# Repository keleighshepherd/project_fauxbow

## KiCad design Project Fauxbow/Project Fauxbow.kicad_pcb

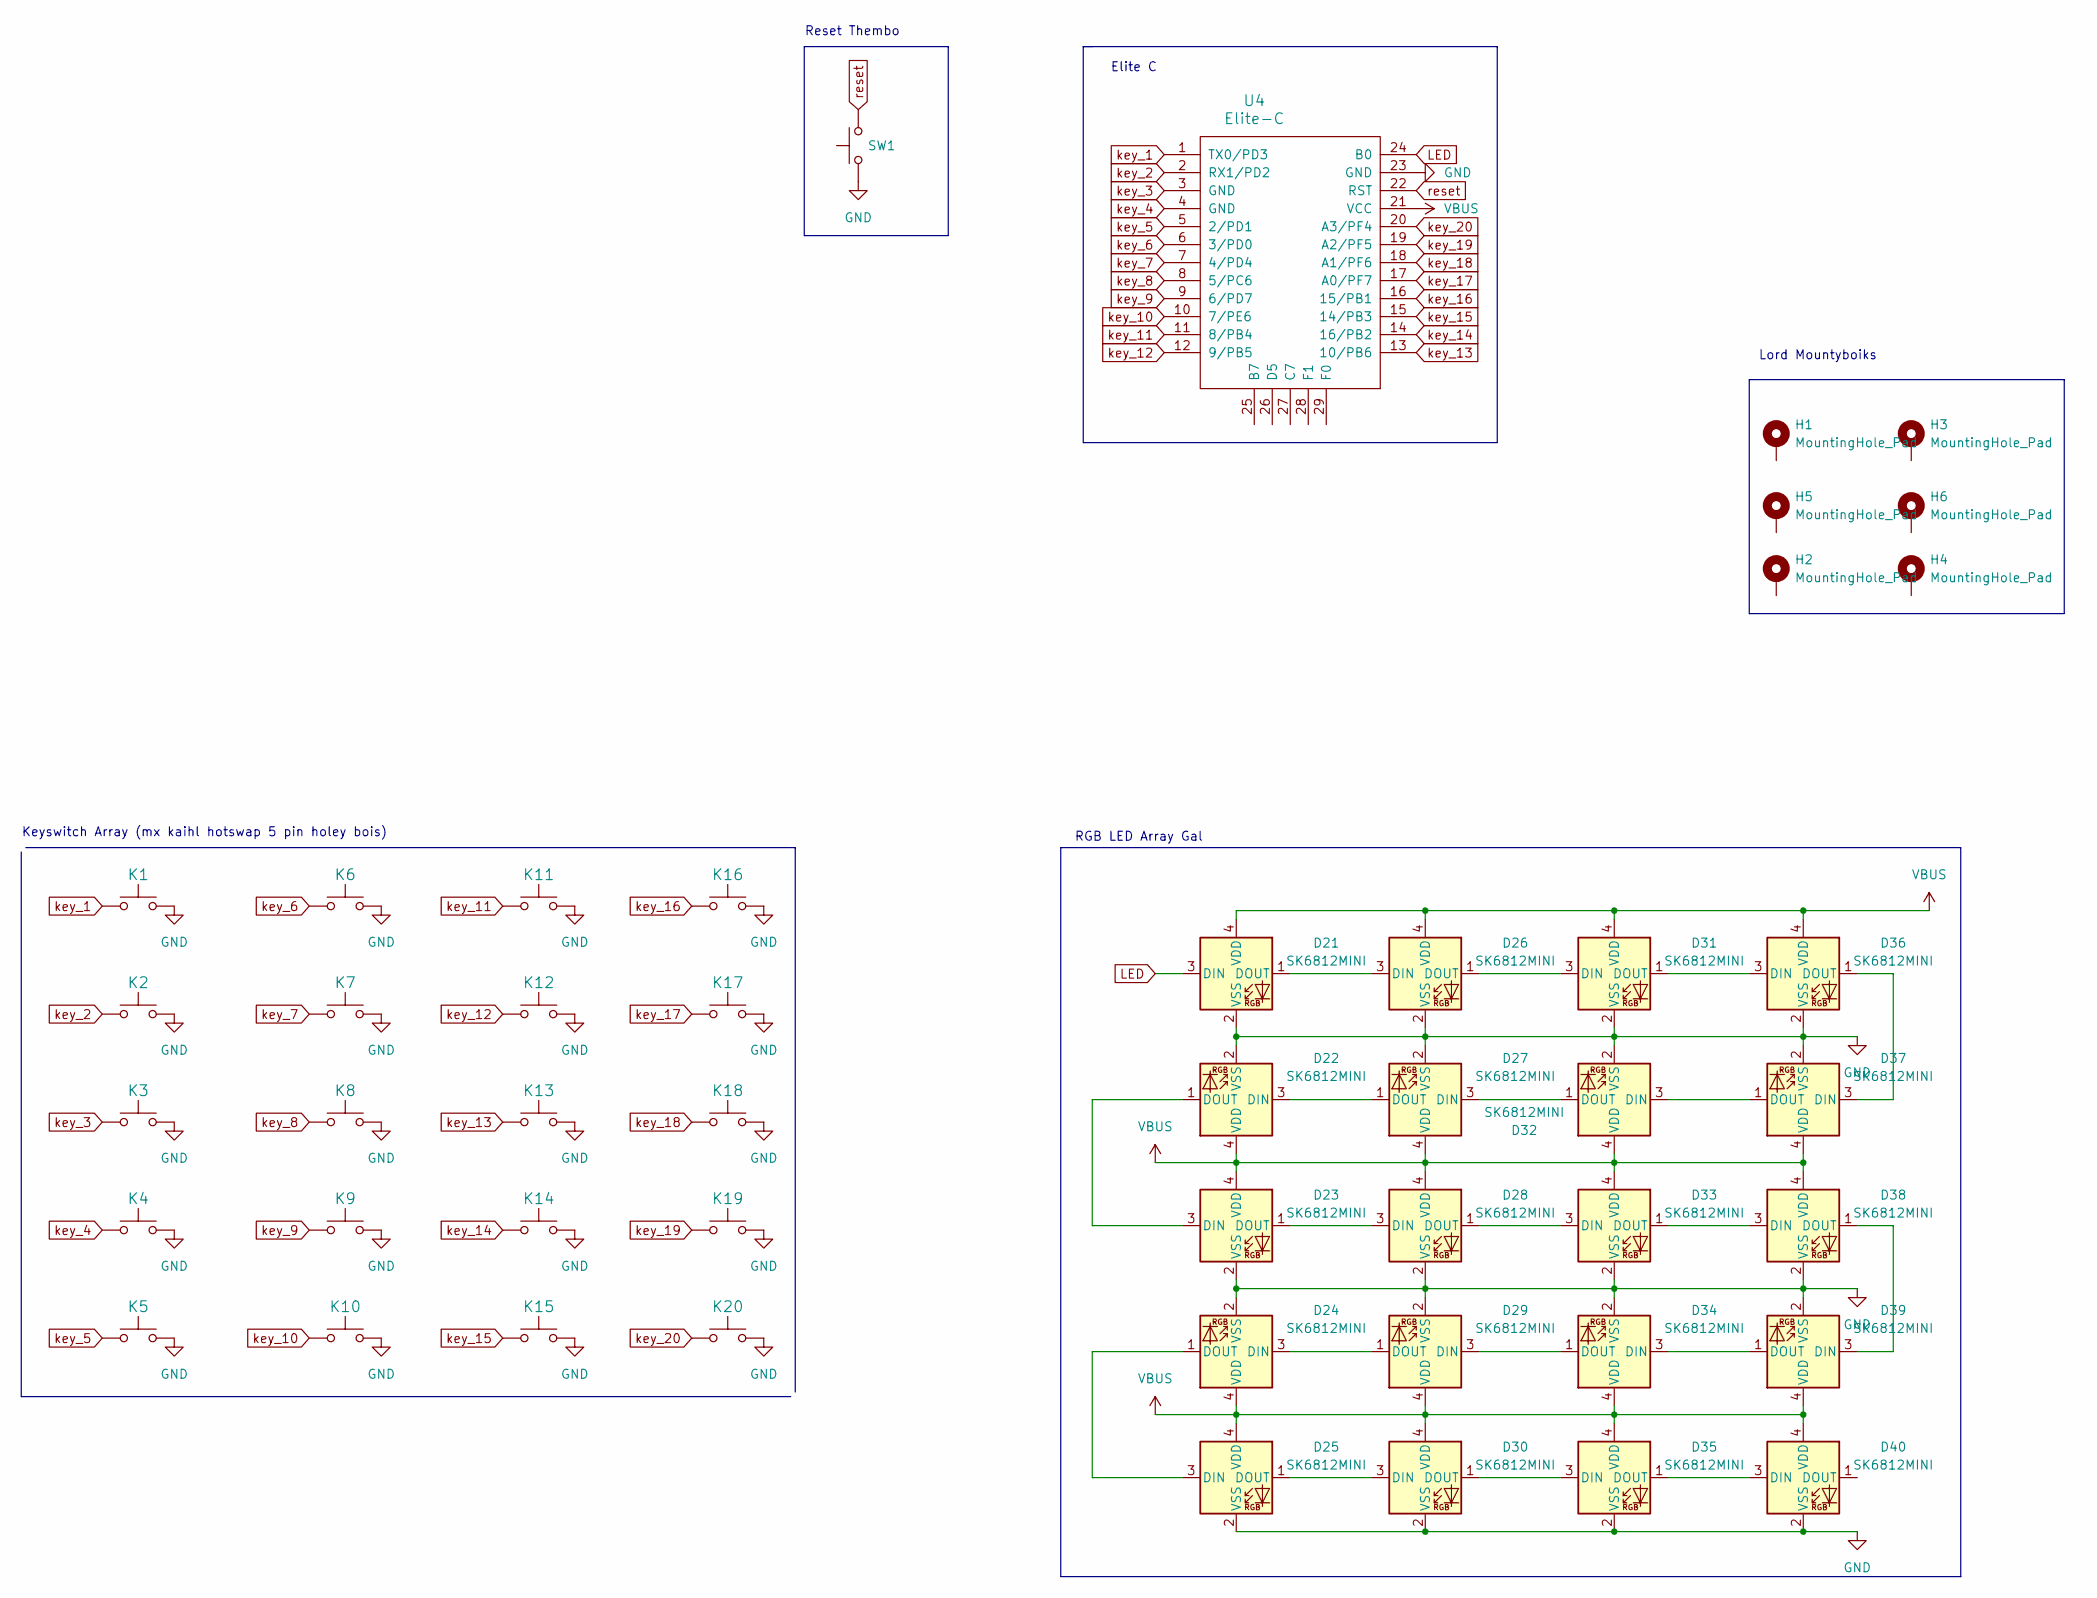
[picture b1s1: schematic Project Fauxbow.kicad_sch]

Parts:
D21, D22, D23, D24, D25, D26, D27, D28, D29, D30, D31, D32, D33, D34, D35, D36, D37, D38, D39, D40: SK6812MINI; LED_MX_6028R-FLIPPED
H1, H2, H3, H4, H5, H6: MountingHole_Pad; MountingHole_2.7mm_M2.5_ISO7380_Pad
K1, K2, K3, K4, K5, K6, K7, K8, K9, K10, K11, K12, K13, K14, K15, K16, K17, K18, K19, K20: Kailh Hotswap Socket; SW_MX_HS_1u; MPN CPG151101S11
SW1: SW_Push; SW_Tactile_SPST_Angled_MJTP1117
U4: Elite-C; Elite-C-castellated-29pin-holes

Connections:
GND: D21.2 (VSS), D22.2 (VSS), D23.2 (VSS), D24.2 (VSS), D25.2 (VSS), D26.2 (VSS), D27.2 (VSS), D28.2 (VSS), D29.2 (VSS), D30.2 (VSS), D31.2 (VSS), D32.2 (VSS), D33.2 (VSS), D34.2 (VSS), D35.2 (VSS), D36.2 (VSS), D37.2 (VSS), D38.2 (VSS), D39.2 (VSS), D40.2 (VSS), K1.1, K2.1, K3.1, K4.1, K5.1, K6.1, K7.1, K8.1, K9.1, K10.1, K11.1, K12.1, K13.1, K14.1, K15.1, K16.1, K17.1, K18.1, K19.1, K20.1, SW1.1, U4.23 (GND)
LED: D21.3 (DIN), U4.24 (B0)
unnamed: D21.1 (DOUT), D26.3 (DIN)
unnamed: D22.1 (DOUT), D23.3 (DIN)
unnamed: D22.3 (DIN), D27.1 (DOUT)
unnamed: D23.1 (DOUT), D28.3 (DIN)
unnamed: D24.1 (DOUT), D25.3 (DIN)
unnamed: D24.3 (DIN), D29.1 (DOUT)
unnamed: D25.1 (DOUT), D30.3 (DIN)
unnamed: D26.1 (DOUT), D31.3 (DIN)
unnamed: D27.3 (DIN), D32.1 (DOUT)
unnamed: D28.1 (DOUT), D33.3 (DIN)
unnamed: D29.3 (DIN), D34.1 (DOUT)
unnamed: D30.1 (DOUT), D35.3 (DIN)
unnamed: D31.1 (DOUT), D36.3 (DIN)
unnamed: D32.3 (DIN), D37.1 (DOUT)
unnamed: D33.1 (DOUT), D38.3 (DIN)
unnamed: D34.3 (DIN), D39.1 (DOUT)
unnamed: D35.1 (DOUT), D40.3 (DIN)
unnamed: D36.1 (DOUT), D37.3 (DIN)
unnamed: D38.1 (DOUT), D39.3 (DIN)
VBUS: D21.4 (VDD), D22.4 (VDD), D23.4 (VDD), D24.4 (VDD), D25.4 (VDD), D26.4 (VDD), D27.4 (VDD), D28.4 (VDD), D29.4 (VDD), D30.4 (VDD), D31.4 (VDD), D32.4 (VDD), D33.4 (VDD), D34.4 (VDD), D35.4 (VDD), D36.4 (VDD), D37.4 (VDD), D38.4 (VDD), D39.4 (VDD), D40.4 (VDD), U4.21 (VCC)
key_1: K1.2, U4.1 (TX0/PD3)
key_2: K2.2, U4.2 (RX1/PD2)
key_3: K3.2, U4.3 (GND)
key_4: K4.2, U4.4 (GND)
key_5: K5.2, U4.5 (2/PD1)
key_6: K6.2, U4.6 (3/PD0)
key_7: K7.2, U4.7 (4/PD4)
key_8: K8.2, U4.8 (5/PC6)
key_9: K9.2, U4.9 (6/PD7)
key_10: K10.2, U4.10 (7/PE6)
key_11: K11.2, U4.11 (8/PB4)
key_12: K12.2, U4.12 (9/PB5)
key_13: K13.2, U4.13 (10/PB6)
key_14: K14.2, U4.14 (16/PB2)
key_15: K15.2, U4.15 (14/PB3)
key_16: K16.2, U4.16 (15/PB1)
key_17: K17.2, U4.17 (A0/PF7)
key_18: K18.2, U4.18 (A1/PF6)
key_19: K19.2, U4.19 (A2/PF5)
key_20: K20.2, U4.20 (A3/PF4)
reset: SW1.2, U4.22 (RST)

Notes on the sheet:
Reset Thembo
Lord Mountyboiks
Keyswitch Array (mx kaihl hotswap 5 pin holey bois)
RGB LED Array Gal
Elite C

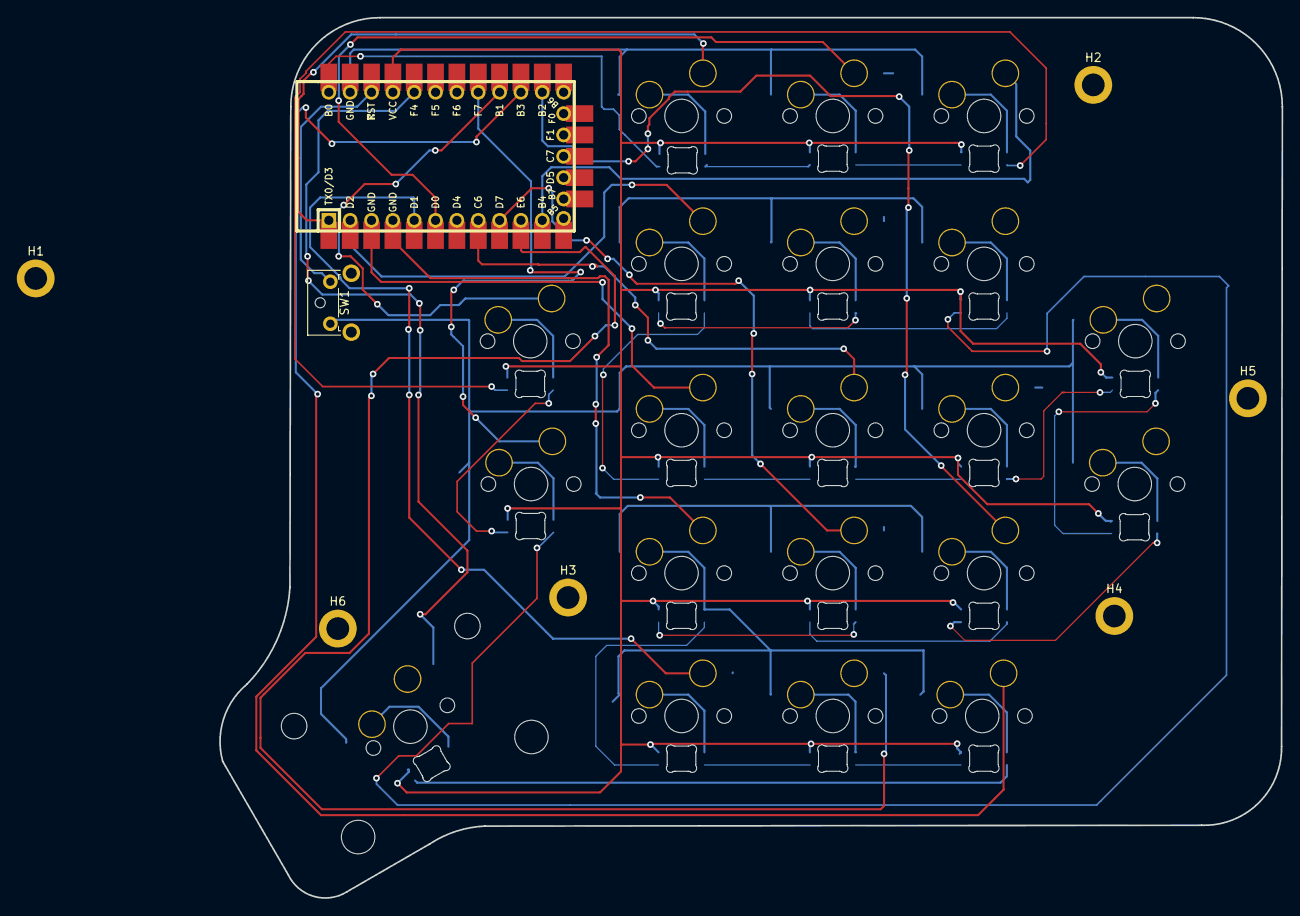
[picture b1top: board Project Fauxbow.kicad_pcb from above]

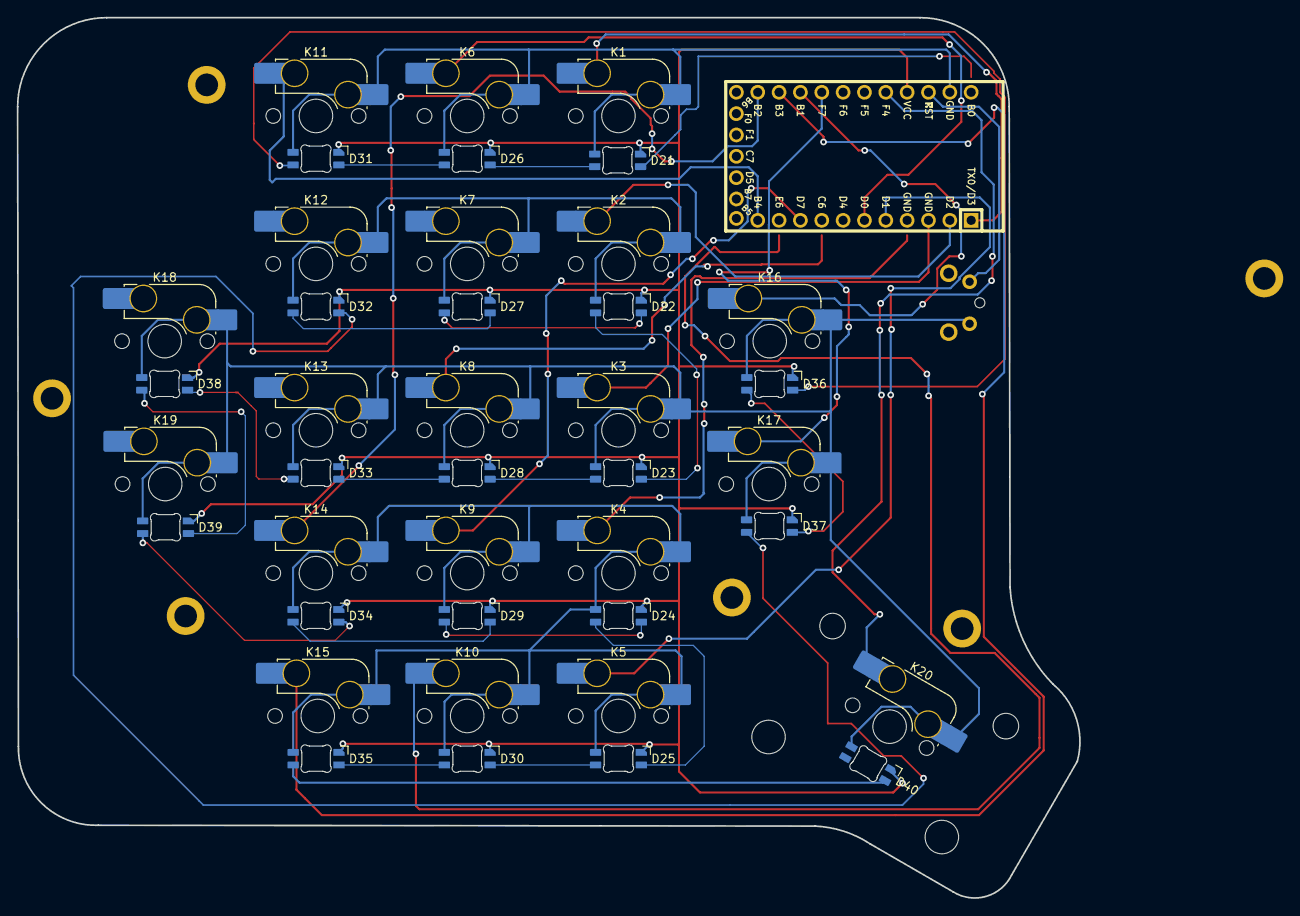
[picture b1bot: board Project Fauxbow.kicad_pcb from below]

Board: 2 copper layers, 126.4 x 104.8 mm, 48 parts (40 on the bottom side), 43 nets.

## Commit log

2022-05-22 loading of stuff
2022-05-23 unified daughterboard zip
2022-06-02 current
2022-06-06 INITIAL COMMIT REV 1
